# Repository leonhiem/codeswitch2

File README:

codeswitch2 firmware compiler options:

(see firmware/codeswitch2/samd11/compiler.png for Atmel Studio)

KEYPAD_INTEGRATED=n  (n=0: membrane keypad n=1: integrated keypad)
LCD=n                (n=0: Bottom          n=1: Top)
TESTING=n            (n=0: no              n=1: yes)

For Helen use:
KEYPAD_INTEGRATED=1
LCD=0

For alt Chinese use:
KEYPAD_INTEGRATED=0
LCD=1

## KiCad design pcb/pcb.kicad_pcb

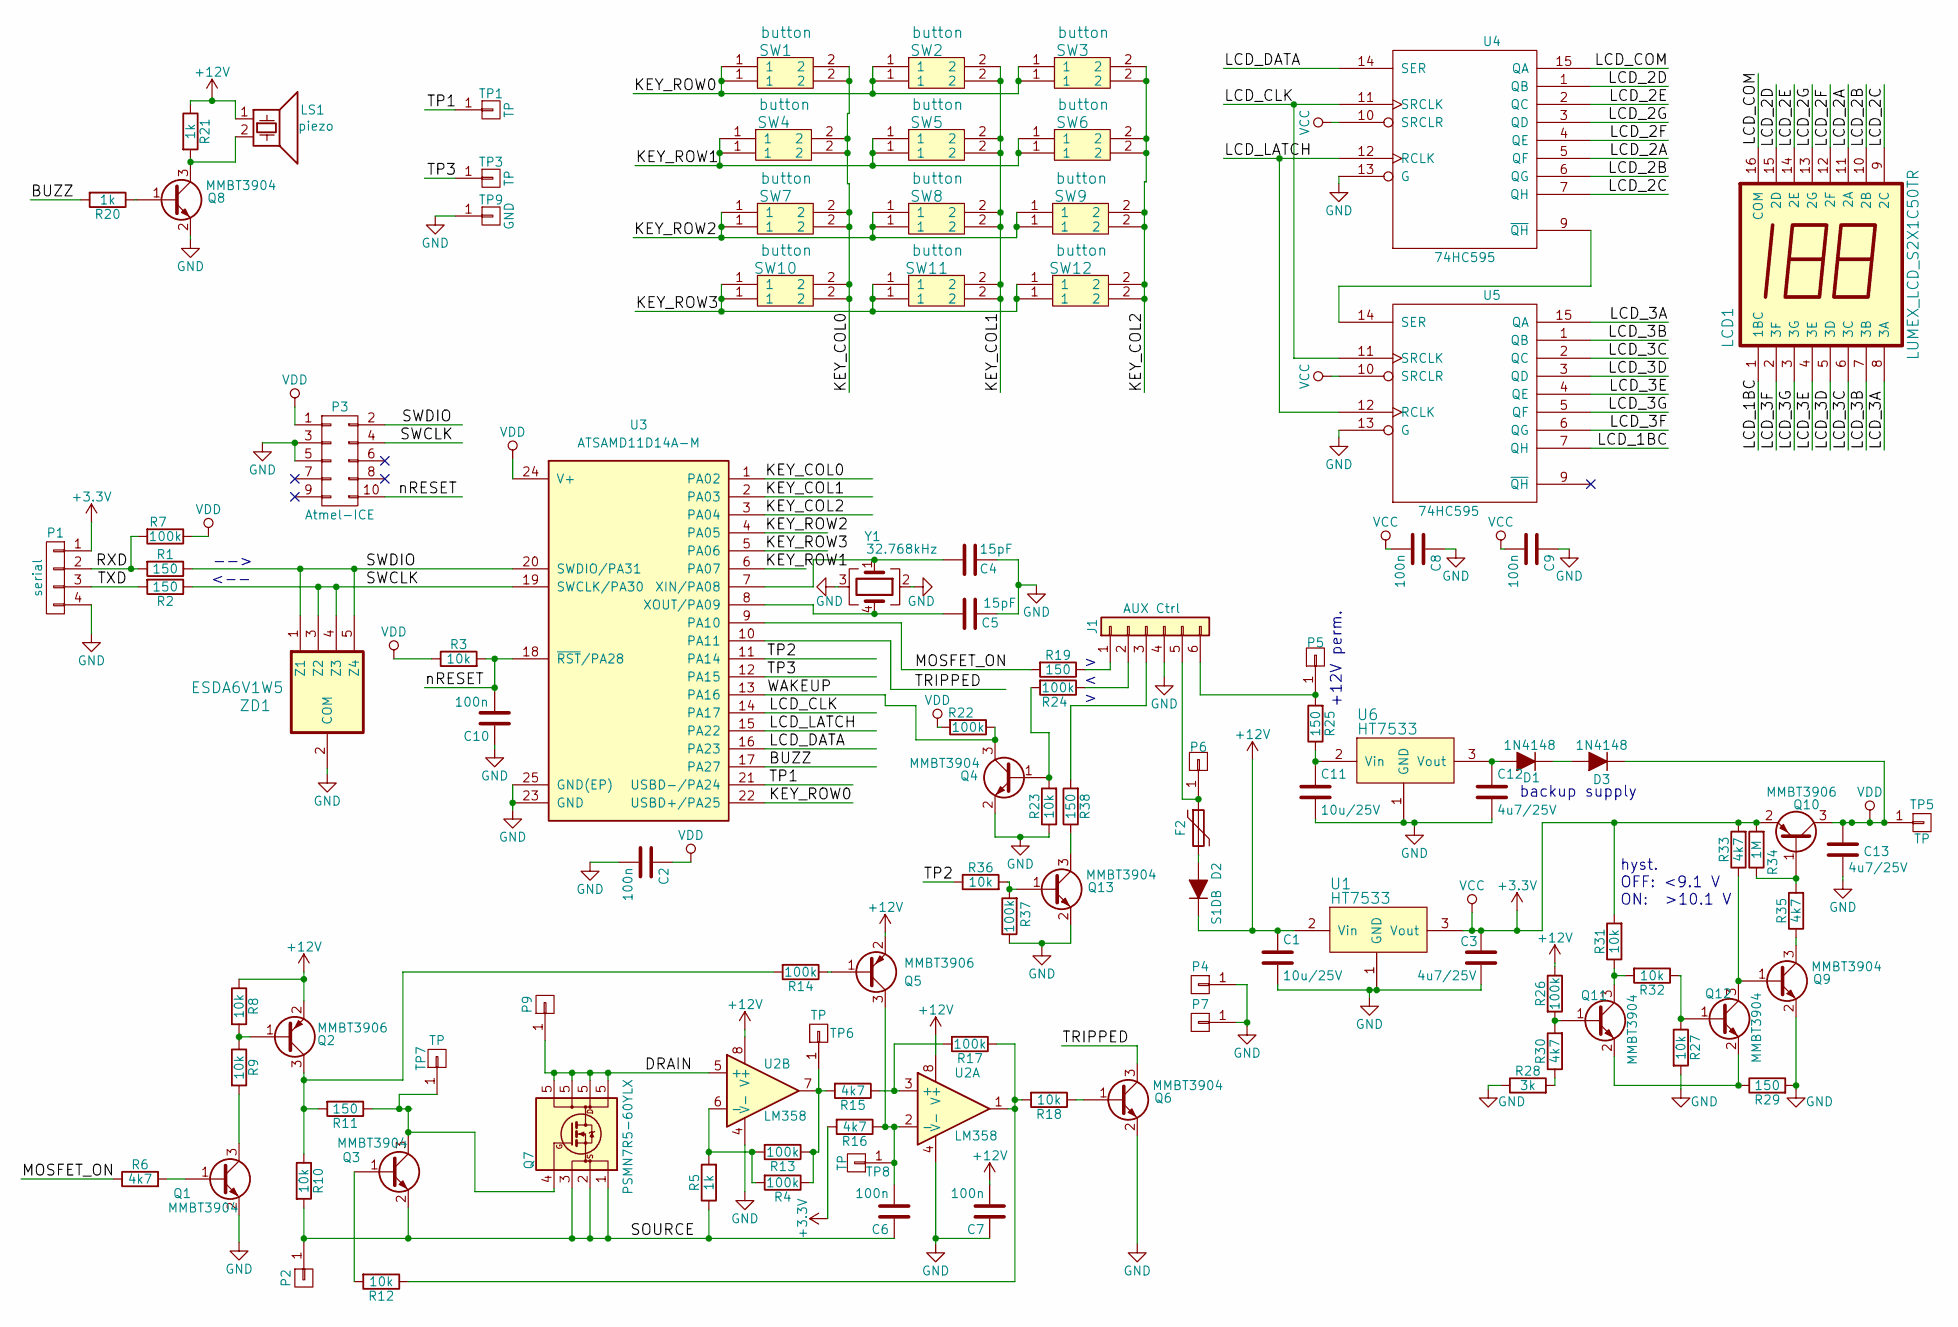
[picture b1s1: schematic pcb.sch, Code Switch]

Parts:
C1, C11: 10u/25V; C_0805_reflow
C2, C6, C7, C8, C9, C10: 100n; C_0805_reflow
C3, C12, C13: 4u7/25V; C_0805_reflow
C4, C5: 15pF; C_0805_reflow
D1, D3: 1N4148; SOD-80A
D2: S1DB; D_SMB_Handsoldering
F2: Polyfuse 1.1A-hold 2.2A-trip; R_1812
J1: AUX Ctrl; Pin_Header_Straight_1x06_Pitch2.54mm
LCD1: LUMEX_LCD_S2X1C50TR
LS1: piezo; MagneticBuzzer_StarMicronics_HMB-06_HMB-12
P1: serial; Pin_Header_Straight_1x04_Pitch2.54mm
P2, P4, P5, P6, P7, P9: (faston male 6.35mm); faston_m_63
P3: Atmel-ICE; Atmel_ICE
Q1, Q3, Q4, Q6, Q8, Q9, Q11, Q12, Q13: MMBT3904; SOT-23
Q2, Q5, Q10: MMBT3906; SOT-23
Q7: PSMN7R5-60YLX; TDSON-8-1_HandSoldering
R1, R2, R11, R19, R25, R29, R38: 150; R_0805_reflow
R3, R8, R9, R10, R12, R18, R23, R27, R31, R32, R36: 10k; R_0805_reflow
R4, R7, R13, R14, R17, R22, R24, R26, R37: 100k; R_0805_reflow
R5, R20, R21: 1k; R_0805_reflow
R6, R15, R16, R30, R33, R35: 4k7; R_0805_reflow
R28: 3k; R_0805_reflow
R34: 1M; R_0805_reflow
SW1, SW2, SW3, SW4, SW5, SW6, SW7, SW8, SW9, SW10, SW11, SW12: button; SW_SPST_keypad
TP1, TP3, TP5, TP6, TP7, TP8: TP; Pin_Header_Straight_1x01_Pitch2.54mm
TP9: GND; Pin_Header_Straight_1x01_Pitch2.54mm
U1, U6: HT7533; SOT-89-3_Handsoldering
U2: LM358; SOIC-8_3.9x4.9mm_Pitch1.27mm
U3: ATSAMD11D14A-M; QFN-24-1EP_4x4mm_Pitch0.5mm
U4, U5: 74HC595; SOIC-16_3.9x9.9mm_Pitch1.27mm
Y1: 32.768kHz; Crystal_SMD_Abracon_4pin_32768khz
ZD1: ESDA6V1W5; SOT-353_SC-70-5_Handsoldering

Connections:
+3V3: C3.1, C8.2, C9.2, P1.1, Q10.2 (E), R16.2, R31.2, R33.2, R34.2, U1.3 (Vout), U4.10 (SRCLR), U4.16 (VCC), U5.10 (SRCLR), U5.16 (VCC)
+12V: C1.1, C7.2, D2.1 (K), LS1.1, Q2.2 (E), Q5.2 (E), R8.1, R21.1, R26.1, U1.2 (Vin), U2.8 (V+)
/BUZZ: R20.2, U3.17 (PA27)
/DRAIN: P9.1, Q7.5 (D), U2.5 (+)
/KEY_COL0: SW1.2, SW4.2, SW7.2, SW10.2, U3.1 (PA02)
/KEY_COL1: SW2.2, SW5.2, SW8.2, SW11.2, U3.2 (PA03)
/KEY_COL2: SW3.2, SW6.2, SW9.2, SW12.2, U3.3 (PA04)
/KEY_ROW0: SW1.1, SW2.1, SW3.1, U3.22 (USBD+/PA25)
/KEY_ROW1: SW4.1, SW5.1, SW6.1, U3.6 (PA07)
/KEY_ROW2: SW7.1, SW8.1, SW9.1, U3.4 (PA05)
/KEY_ROW3: SW10.1, SW11.1, SW12.1, U3.5 (PA06)
/LCD_1BC: LCD1.1 (1BC), U5.7 (QH)
/LCD_2A: LCD1.11 (2A), U4.5 (QF)
/LCD_2B: LCD1.10 (2B), U4.6 (QG)
/LCD_2C: LCD1.9 (2C), U4.7 (QH)
/LCD_2D: LCD1.15 (2D), U4.1 (QB)
/LCD_2E: LCD1.14 (2E), U4.2 (QC)
/LCD_2F: LCD1.12 (2F), U4.4 (QE)
/LCD_2G: LCD1.13 (2G), U4.3 (QD)
/LCD_3A: LCD1.8 (3A), U5.15 (QA)
/LCD_3B: LCD1.7 (3B), U5.1 (QB)
/LCD_3C: LCD1.6 (3C), U5.2 (QC)
/LCD_3D: LCD1.5 (3D), U5.3 (QD)
/LCD_3E: LCD1.4 (3E), U5.4 (QE)
/LCD_3F: LCD1.2 (3F), U5.6 (QG)
/LCD_3G: LCD1.3 (3G), U5.5 (QF)
/LCD_CLK: U3.14 (PA17), U4.11 (SRCLK), U5.11 (SRCLK)
/LCD_COM: LCD1.16 (COM), U4.15 (QA)
/LCD_DATA: U3.16 (PA23), U4.14 (SER)
/LCD_LATCH: U3.15 (PA22), U4.12 (RCLK), U5.12 (RCLK)
/MOSFET_ON: R6.1, R19.2, U3.9 (PA10)
/RXD: P1.2, R1.2, R7.2
/SOURCE: C6.1, P2.1, Q3.2 (E), Q7.1 (S), Q7.2 (S), Q7.3 (S), R5.1, R10.2
/SWCLK: P3.4, R2.1, U3.19 (SWCLK/PA30), ZD1.3 (Z2), ZD1.4 (Z3)
/SWDIO: P3.2, R1.1, U3.20 (SWDIO/PA31), ZD1.1 (Z1), ZD1.5 (Z4)
/TP1: TP1.1, U3.21 (USBD-/PA24)
/TP2: R36.1, U3.11 (PA14)
/TP3: TP3.1, U3.12 (PA15)
/TRIPPED: Q6.3 (C), U3.10 (PA11)
/TXD: P1.3, R2.2
/WAKEUP: Q4.3 (C), R22.1, U3.13 (PA16)
/nRESET: C10.2, P3.10, R3.2, U3.18 (~RST~/PA28)
GND: C1.2, C2.2, C3.2, C4.1, C5.1, C7.1, C8.1, C9.1, C10.1, C11.2, C12.2, C13.2, J1.4, P1.4, P3.3, P3.5, P4.1, P7.1, Q1.2 (E), Q4.2 (E), Q6.2 (E), Q8.2 (E), Q9.2 (E), Q13.2 (E), R23.1, R27.2, R28.1, R29.2, R37.1, TP9.1, U1.1 (GND), U2.4 (V-), U3.23 (GND), U3.25 (GND(EP)), U4.8 (GND), U4.13 (G), U5.8 (GND), U5.13 (G), U6.1 (GND), Y1.2, Y1.3, ZD1.2 (COM)
unnamed: C4.2, U3.7 (XIN/PA08), Y1.1
unnamed: C5.2, U3.8 (XOUT/PA09), Y1.4
unnamed: C6.2, Q5.3 (C), R16.1, TP8.1, U2.2 (-)
unnamed: C11.1, R25.1, U6.2 (Vin)
unnamed: C12.1, D1.2 (A), U6.3 (Vout)
unnamed: D1.1 (K), D3.2 (A)
unnamed: D2.2 (A), F2.2
unnamed: F2.1, J1.5, P6.1
unnamed: J1.1, R19.1
unnamed: J1.2, R24.1
unnamed: J1.3, R38.2
unnamed: J1.6, P5.1, R25.2
unnamed: LS1.2, Q8.3 (C), R21.2
unnamed: Q1.1 (B), R6.2
unnamed: Q1.3 (C), R9.2
unnamed: Q2.1 (B), R8.2, R9.1
unnamed: Q2.3 (C), R10.1, R11.2, R14.2
unnamed: Q3.1 (B), R12.2
unnamed: Q3.3 (C), Q7.4 (G), R11.1, TP7.1
unnamed: Q4.1 (B), R23.2, R24.2
unnamed: Q5.1 (B), R14.1
unnamed: Q6.1 (B), R18.1
unnamed: Q8.1 (B), R20.1
unnamed: Q9.3 (C), R35.1
unnamed: Q10.1 (B), R34.1, R35.2
unnamed: Q11.1 (B), R26.2, R30.2
unnamed: Q11.2 (E), Q12.2 (E), R29.1
unnamed: Q11.3 (C), R31.1, R32.2
unnamed: Q12.1 (B), R27.1, R32.1
unnamed: Q9.1 (B), Q12.3 (C), R33.1
unnamed: Q13.1 (B), R36.2, R37.2
unnamed: Q13.3 (C), R38.1
unnamed: R12.1, R17.1, R18.2, U2.1
unnamed: R4.1, R13.1, R15.2, TP6.1, U2.7
unnamed: R4.2, R5.2, R13.2, U2.6 (-)
unnamed: R15.1, R17.2, U2.3 (+)
unnamed: R28.2, R30.1
unnamed: U4.9 (~QH), U5.14 (SER)
VDD: C2.1, C13.1, D3.1 (K), P3.1, Q10.3 (C), R3.1, R7.1, R22.2, TP5.1, U3.24 (V+)

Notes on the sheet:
-->
<--
backup supply
+12V perm.
hyst. OFF: <9.1 V ON: >10.1 V

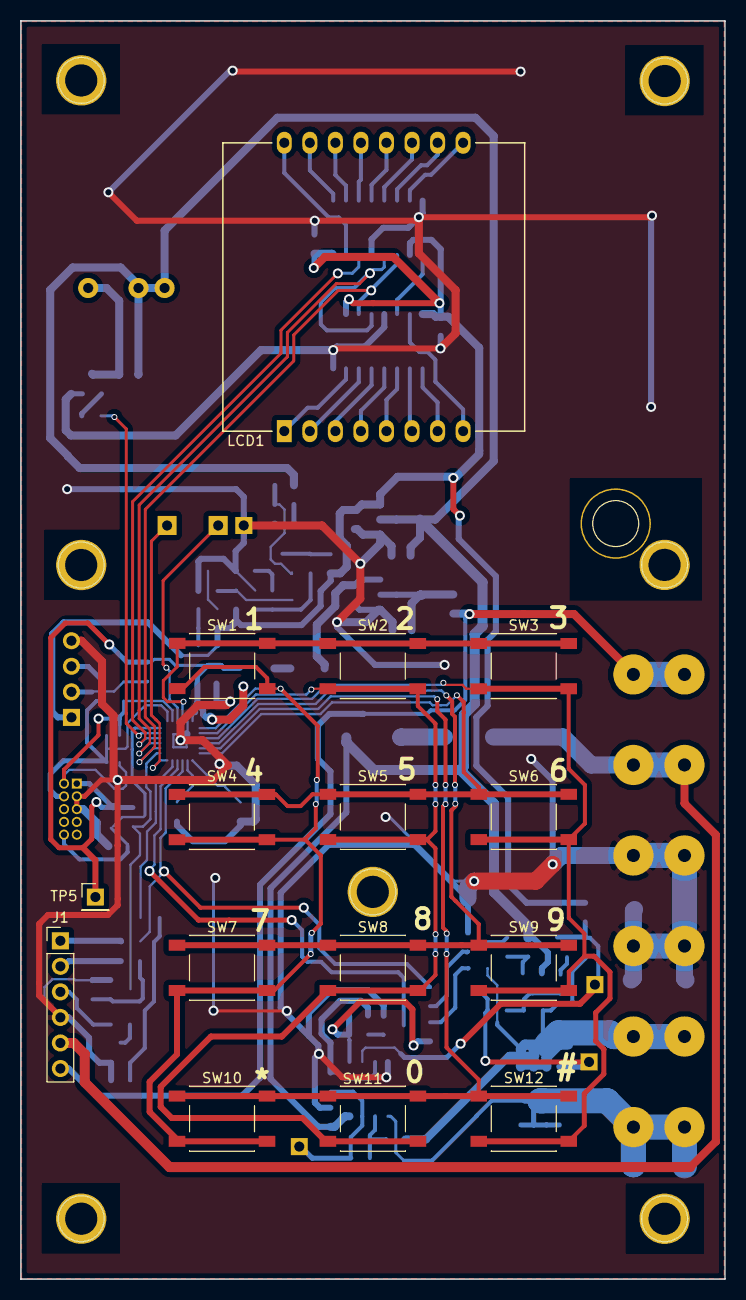
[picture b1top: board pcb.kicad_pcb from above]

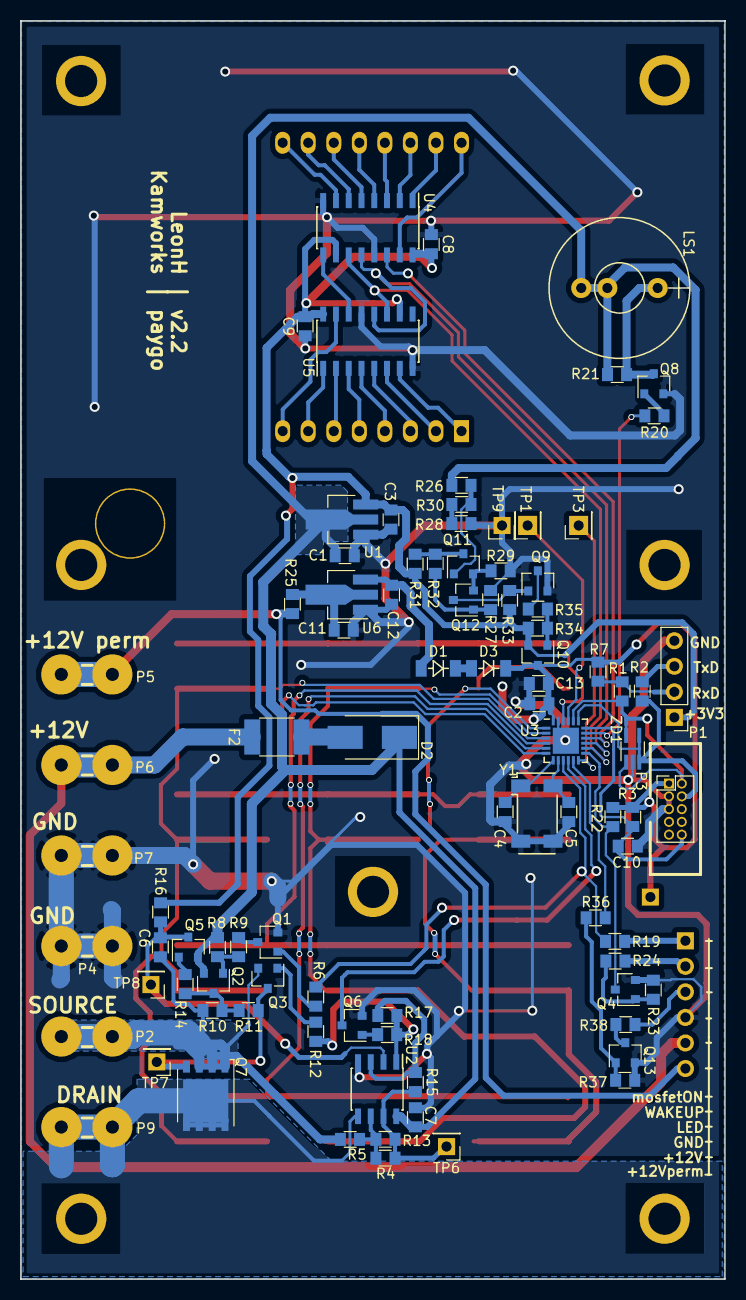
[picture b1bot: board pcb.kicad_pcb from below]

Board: 2 copper layers, 70.0 x 125.1 mm, 106 parts (91 on the bottom side), 82 nets.

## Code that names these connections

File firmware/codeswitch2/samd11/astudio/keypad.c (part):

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}

/*
HAL_GPIO_PIN(KEY_COL0, A, 14)
HAL_GPIO_PIN(KEY_COL1, A, 15)
HAL_GPIO_PIN(KEY_COL2, A, 16)
HAL_GPIO_PIN(KEY_ROW3, A, 17)
HAL_GPIO_PIN(KEY_ROW2, A, 22)
HAL_GPIO_PIN(KEY_ROW1, A, 23)
HAL_GPIO_PIN(KEY_ROW0, A, 27)
*/
// Private : Hardware scan
void keypad_scanKeys() {
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            //bitWrite(bitMap[r], c, !pin_read(rowPins[r]));  // keypress is active low so invert to high.
            bitWrite(bitMap[r], c, !((PORT->Group[HAL_GPIO_PORTA].IN.reg & (1 << rowPins[r])) != 0));  // keypress is active low so invert to high.
        }
        //same as: uint8_t tripped = HAL_GPIO_TRIPPED_PIN_read() :=
        //return (PORT->Group[HAL_GPIO_PORTA].IN.reg & (1 << rowPins[r])) != 0;
        
        
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
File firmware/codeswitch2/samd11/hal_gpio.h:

/*
 * Copyright (c) 2014-2016, Alex Taradov <alex@taradov.com>
 * All rights reserved.
 *
 * Redistribution and use in source and binary forms, with or without
 * modification, are permitted provided that the following conditions are met:
 *
 * 1. Redistributions of source code must retain the above copyright notice,
 *    this list of conditions and the following disclaimer.
 * 2. Redistributions in binary form must reproduce the above copyright
 *    notice, this list of conditions and the following disclaimer in the
 *    documentation and/or other materials provided with the distribution.
 * 3. The name of the author may not be used to endorse or promote products
 *    derived from this software without specific prior written permission.
 *
 * THIS SOFTWARE IS PROVIDED BY THE COPYRIGHT HOLDERS AND CONTRIBUTORS "AS IS"
 * AND ANY EXPRESS OR IMPLIED WARRANTIES, INCLUDING, BUT NOT LIMITED TO, THE
 * IMPLIED WARRANTIES OF MERCHANTABILITY AND FITNESS FOR A PARTICULAR PURPOSE
 * ARE DISCLAIMED. IN NO EVENT SHALL THE COPYRIGHT HOLDER OR CONTRIBUTORS BE
 * LIABLE FOR ANY DIRECT, INDIRECT, INCIDENTAL, SPECIAL, EXEMPLARY, OR
 * CONSEQUENTIAL DAMAGES (INCLUDING, BUT NOT LIMITED TO, PROCUREMENT OF
 * SUBSTITUTE GOODS OR SERVICES; LOSS OF USE, DATA, OR PROFITS; OR BUSINESS
 * INTERRUPTION) HOWEVER CAUSED AND ON ANY THEORY OF LIABILITY, WHETHER IN
 * CONTRACT, STRICT LIABILITY, OR TORT (INCLUDING NEGLIGENCE OR OTHERWISE)
 * ARISING IN ANY WAY OUT OF THE USE OF THIS SOFTWARE, EVEN IF ADVISED OF THE
 * POSSIBILITY OF SUCH DAMAGE.
 */

#ifndef _HAL_GPIO_H_
#define _HAL_GPIO_H_

/*- Definitions -------------------------------------------------------------*/
#define HAL_GPIO_PORTA       0
#define HAL_GPIO_PORTB       1
#define HAL_GPIO_PORTC       2

#define HAL_GPIO_PMUX_A      0
#define HAL_GPIO_PMUX_B      1
#define HAL_GPIO_PMUX_C      2
#define HAL_GPIO_PMUX_D      3
#define HAL_GPIO_PMUX_E      4
#define HAL_GPIO_PMUX_F      5
#define HAL_GPIO_PMUX_G      6
#define HAL_GPIO_PMUX_H      7
#define HAL_GPIO_PMUX_I      8

#define HAL_GPIO_PIN(name, port, pin)						\
  static inline void HAL_GPIO_##name##_set(void)				\
  {										\
    PORT->Group[HAL_GPIO_PORT##port].OUTSET.reg = (1 << pin);			\
    (void)HAL_GPIO_##name##_set;						\
  }										\
										\
  static inline void HAL_GPIO_##name##_clr(void)				\
  {										\
    PORT->Group[HAL_GPIO_PORT##port].OUTCLR.reg = (1 << pin);			\
    (void)HAL_GPIO_##name##_clr;						\
  }										\
										\
  static inline void HAL_GPIO_##name##_toggle(void)				\
  {										\
    PORT->Group[HAL_GPIO_PORT##port].OUTTGL.reg = (1 << pin);			\
    (void)HAL_GPIO_##name##_toggle;						\
  }										\
										\
  static inline void HAL_GPIO_##name##_write(int value)				\
  {										\
    if (value)									\
      PORT->Group[HAL_GPIO_PORT##port].OUTSET.reg = (1 << pin);			\
    else									\
      PORT->Group[HAL_GPIO_PORT##port].OUTCLR.reg = (1 << pin);			\
    (void)HAL_GPIO_##name##_write;						\
  }										\
										\
  static inline void HAL_GPIO_##name##_in(void)					\
  {										\
    PORT->Group[HAL_GPIO_PORT##port].DIRCLR.reg = (1 << pin);			\
    PORT->Group[HAL_GPIO_PORT##port].PINCFG[pin].reg |= PORT_PINCFG_INEN;	\
    PORT->Group[HAL_GPIO_PORT##port].PINCFG[pin].reg &= ~PORT_PINCFG_PULLEN;	\
    (void)HAL_GPIO_##name##_in;							\
  }										\
										\
  static inline void HAL_GPIO_##name##_disable(void)					\
  {										\
      PORT->Group[HAL_GPIO_PORT##port].DIRCLR.reg = (1 << pin);			\
      PORT->Group[HAL_GPIO_PORT##port].PINCFG[pin].reg &= ~PORT_PINCFG_INEN;	\
      PORT->Group[HAL_GPIO_PORT##port].PINCFG[pin].reg &= ~PORT_PINCFG_PULLEN;	\
      PORT->Group[HAL_GPIO_PORT##port].PINCFG[pin].reg &= ~PORT_PINCFG_PMUXEN;	\
      (void)HAL_GPIO_##name##_disable;							\
  } \
  \
  static inline void HAL_GPIO_##name##_out(void)				\
  {										\
    PORT->Group[HAL_GPIO_PORT##port].DIRSET.reg = (1 << pin);			\
    PORT->Group[HAL_GPIO_PORT##port].PINCFG[pin].reg |= PORT_PINCFG_INEN;	\
    (void)HAL_GPIO_##name##_out;						\
  }										\
										\
  static inline void HAL_GPIO_##name##_pullup(void)				\
  {										\
    PORT->Group[HAL_GPIO_PORT##port].OUTSET.reg = (1 << pin);			\
    PORT->Group[HAL_GPIO_PORT##port].PINCFG[pin].reg |= PORT_PINCFG_PULLEN;	\
    (void)HAL_GPIO_##name##_pullup;						\
  }										\
										\
  static inline int HAL_GPIO_##name##_read(void)				\
  {										\
    return (PORT->Group[HAL_GPIO_PORT##port].IN.reg & (1 << pin)) != 0;		\
    (void)HAL_GPIO_##name##_read;						\
  }										\
										\
  static inline int HAL_GPIO_##name##_state(void)				\
  {										\
    return (PORT->Group[HAL_GPIO_PORT##port].DIR.reg & (1 << pin)) != 0;	\
    (void)HAL_GPIO_##name##_state;						\
  }										\
										\
  static inline void HAL_GPIO_##name##_pmuxen(int mux)				\
  {										\
    PORT->Group[HAL_GPIO_PORT##port].PINCFG[pin].reg |= PORT_PINCFG_PMUXEN;	\
    if (pin & 1)								\
      PORT->Group[HAL_GPIO_PORT##port].PMUX[pin>>1].bit.PMUXO = mux;		\
    else									\
      PORT->Group[HAL_GPIO_PORT##port].PMUX[pin>>1].bit.PMUXE = mux;		\
    (void)HAL_GPIO_##name##_pmuxen;						\
  }										\
										\
  static inline void HAL_GPIO_##name##_pmuxdis(void)				\
  {										\
    PORT->Group[HAL_GPIO_PORT##port].PINCFG[pin].reg &= ~PORT_PINCFG_PMUXEN;	\
    (void)HAL_GPIO_##name##_pmuxdis;						\
  }										\



HAL_GPIO_PIN(MOSFET_ON,  A, 10)
HAL_GPIO_PIN(UART_TX,   A, 30)
HAL_GPIO_PIN(UART_RX,   A, 31)

#if (KEYPAD_INTEGRATED==1) // keypad pcb with integrated keypad
HAL_GPIO_PIN(WAKEUP_PIN, A, 16)
HAL_GPIO_PIN(PIEZO_PIN, A, 27)

HAL_GPIO_PIN(LCD_DATA,  A, 23)
HAL_GPIO_PIN(LCD_CLK,   A, 17)
HAL_GPIO_PIN(LCD_LATCH, A, 22)

//HAL_GPIO_PIN(LED_RED,   A, 16)
//HAL_GPIO_PIN(TP4, A, 16)
HAL_GPIO_PIN(TP3, A, 15)
HAL_GPIO_PIN(TP2, A, 14)
HAL_GPIO_PIN(TP1, A, 24)

#elif (KEYPAD_INTEGRATED==0) // keypad pcb version with membrane keypad
HAL_GPIO_PIN(WAKEUP_PIN, A, 11)
HAL_GPIO_PIN(PIEZO_PIN, A, 7)

HAL_GPIO_PIN(LCD_DATA,  A, 2)
HAL_GPIO_PIN(LCD_CLK,   A, 24)
HAL_GPIO_PIN(LCD_LATCH, A, 25)

//HAL_GPIO_PIN(LED_RED,   A, 3)
HAL_GPIO_PIN(TP4, A, 3)
HAL_GPIO_PIN(TP3, A, 4)
HAL_GPIO_PIN(TP2, A, 5)
HAL_GPIO_PIN(TP1, A, 6)
#endif

#endif // _HAL_GPIO_H_

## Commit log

2021-10-01 commit from working version
